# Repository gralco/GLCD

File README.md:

Reimplementation of the RepRapDiscount Full Graphic Smart Controller in KiCad

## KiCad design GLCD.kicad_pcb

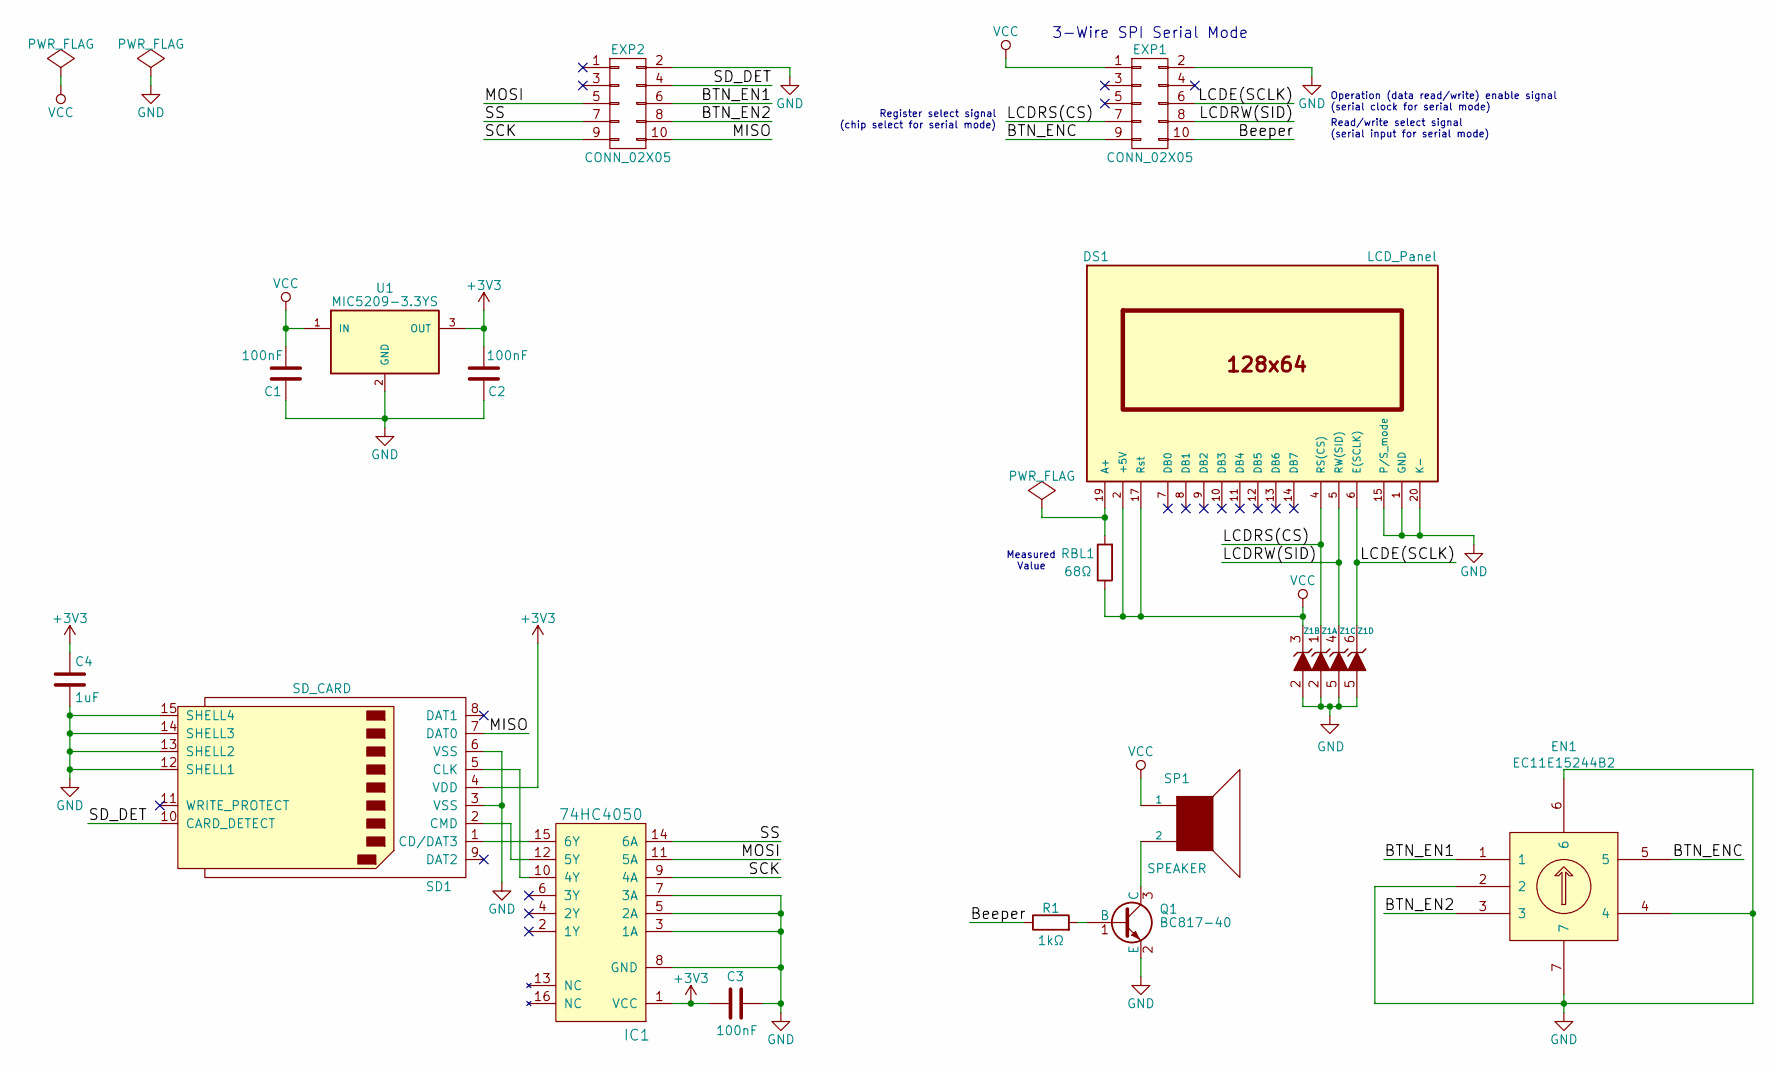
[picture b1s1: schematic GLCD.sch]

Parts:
C1, C2, C3: 100nF; C_0805_HandSoldering; Tolerance 10%; MFG Part Num 08055C104KAT2A
C4: 1uF; C_1206_HandSoldering; Tolerance 5%; MFG Part Num VJ1206Y105JXJTW1BC
DS1: LCD_Panel; Pin_Header_Straight_1x20; MFG Part Num ST7920
EN1: EC11E15244B2; Rotary_Encoder; MFG Part Num EC11E15244B2
EXP1, EXP2: CONN_02X05; IDC_Header_Straight_10pins; MFG Part Num 30310-6002HB
IC1: 74HC4050; SO-16-N; MFG Part Num CD74HC4050M96
Q1: BC817-40; SOT-23_Handsoldering; MFG Part Num BC817-40-7-F
R1: 1kΩ; R_0805_HandSoldering; Tolerance 1%; MFG Part Num CRCW08051K00FKEA
RBL1: 68Ω; R_0805_HandSoldering; Tolerance 5%; MFG Part Num ERJ-6GEYJ680V
SD1: SD_CARD; SD_Card_Receptacle; MFG Part Num 2041021-4
SP1: SPEAKER; Buzzer_12x9.5RM7.6; MFG Part Num AI-1223-TWT-5V-R
U1: MIC5209-3.3YS; SOT-223; MFG Part Num MIC5209-3.3YS-TR
Z1: ZENER_4_CHANNEL; SOT-666; MFG Part Num UCLAMP0504A.TCT

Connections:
+3V3: C2.1, C3.1, C4.1, IC1.1 (VCC), SD1.4 (VDD), U1.3 (OUT)
/BTN_EN1: EN1.1, EXP2.6
/BTN_EN2: EN1.3, EXP2.8
/BTN_ENC: EN1.5, EXP1.9
/Beeper: EXP1.10, R1.1
/LCDE(SCLK): DS1.6 (E(SCLK)), EXP1.6, Z1.6 (K)
/LCDRS(CS): DS1.4 (RS(CS)), EXP1.7, Z1.1 (K)
/LCDRW(SID): DS1.5 (RW(SID)), EXP1.8, Z1.4 (K)
/MISO: EXP2.10, SD1.7 (DAT0)
/MOSI: EXP2.5, IC1.11 (5A)
/SCK: EXP2.9, IC1.9 (4A)
/SD_DET: EXP2.4, SD1.10 (CARD_DETECT)
/SS: EXP2.7, IC1.14 (6A)
GND: C1.2, C2.2, C3.2, C4.2, DS1.1 (GND), DS1.15 (P/S_mode), DS1.20 (K-), EN1.2, EN1.4, EN1.6, EN1.7, EXP1.2, EXP2.2, IC1.3 (1A), IC1.5 (2A), IC1.7 (3A), IC1.8 (GND), Q1.2 (E), SD1.3 (VSS), SD1.6 (VSS), SD1.12 (SHELL1), SD1.13 (SHELL2), SD1.14 (SHELL3), SD1.15 (SHELL4), U1.2 (GND), U1.4, Z1.2 (A), Z1.5 (A)
unnamed: DS1.19 (A+), RBL1.2
unnamed: IC1.10 (4Y), SD1.5 (CLK)
unnamed: IC1.12 (5Y), SD1.2 (CMD)
unnamed: IC1.15 (6Y), SD1.1 (CD/DAT3)
unnamed: Q1.1 (B), R1.2
unnamed: Q1.3 (C), SP1.2
VCC: C1.1, DS1.2 (+5V), DS1.17 (Rst), EXP1.1, RBL1.1, SP1.1, U1.1 (IN), Z1.3 (K)

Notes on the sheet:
Operation (data read/write) enable signal (serial clock for serial mode)
Read/write select signal (serial input for serial mode)
Register select signal (chip select for serial mode)
3-Wire SPI Serial Mode
Measured Value

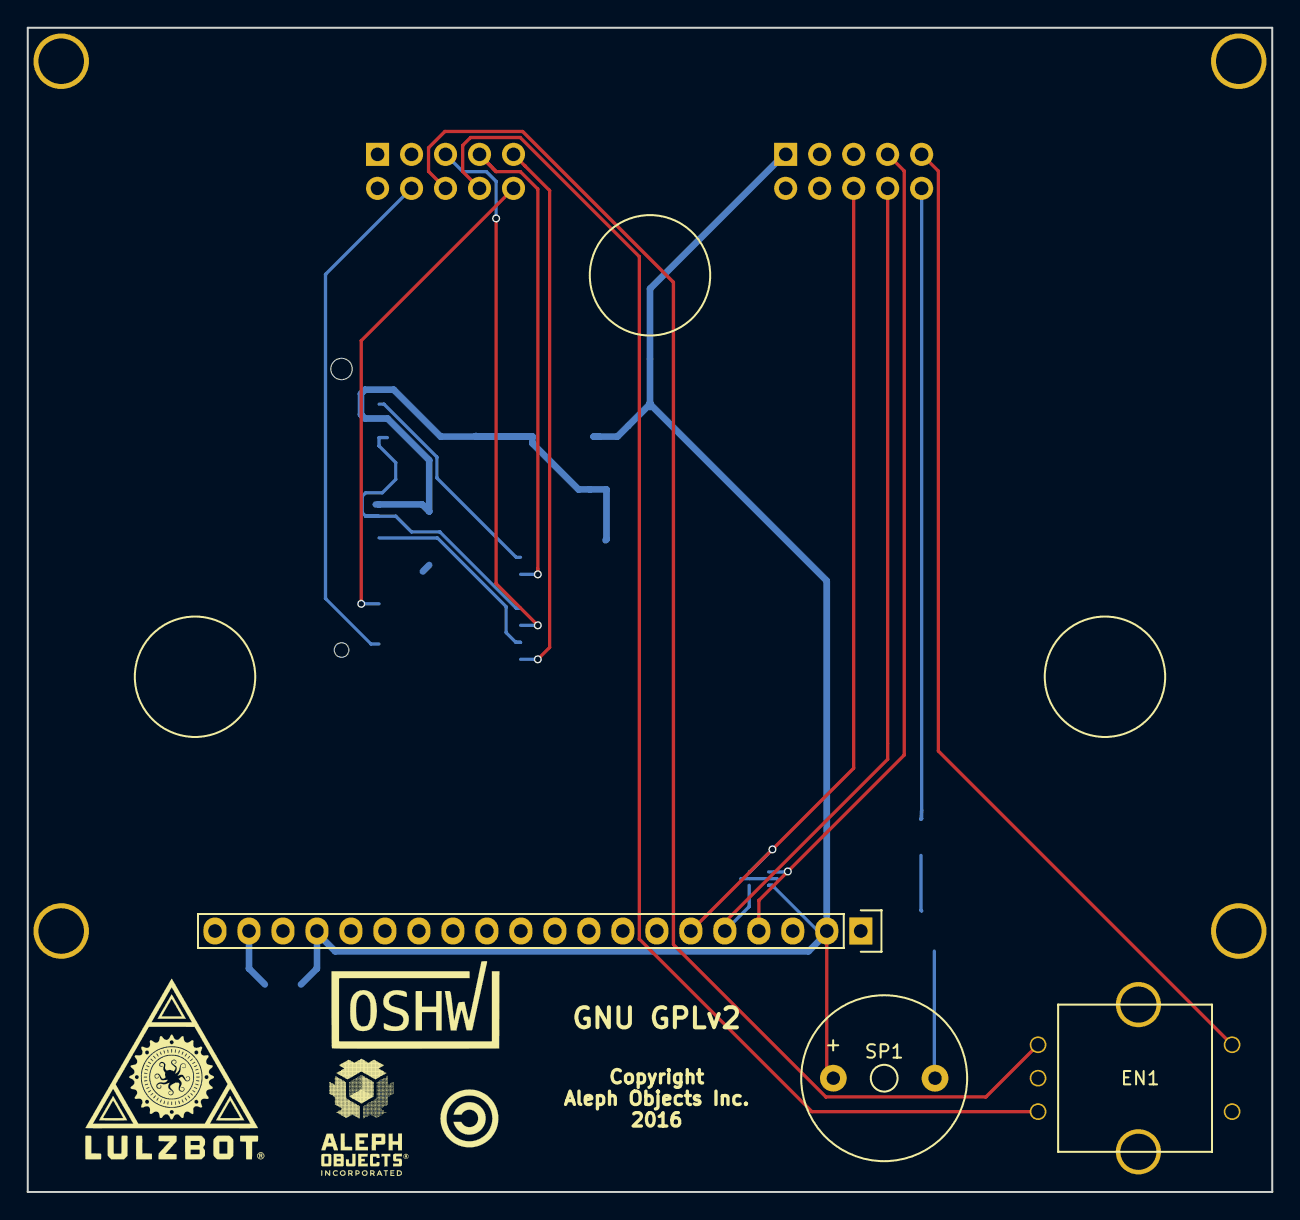
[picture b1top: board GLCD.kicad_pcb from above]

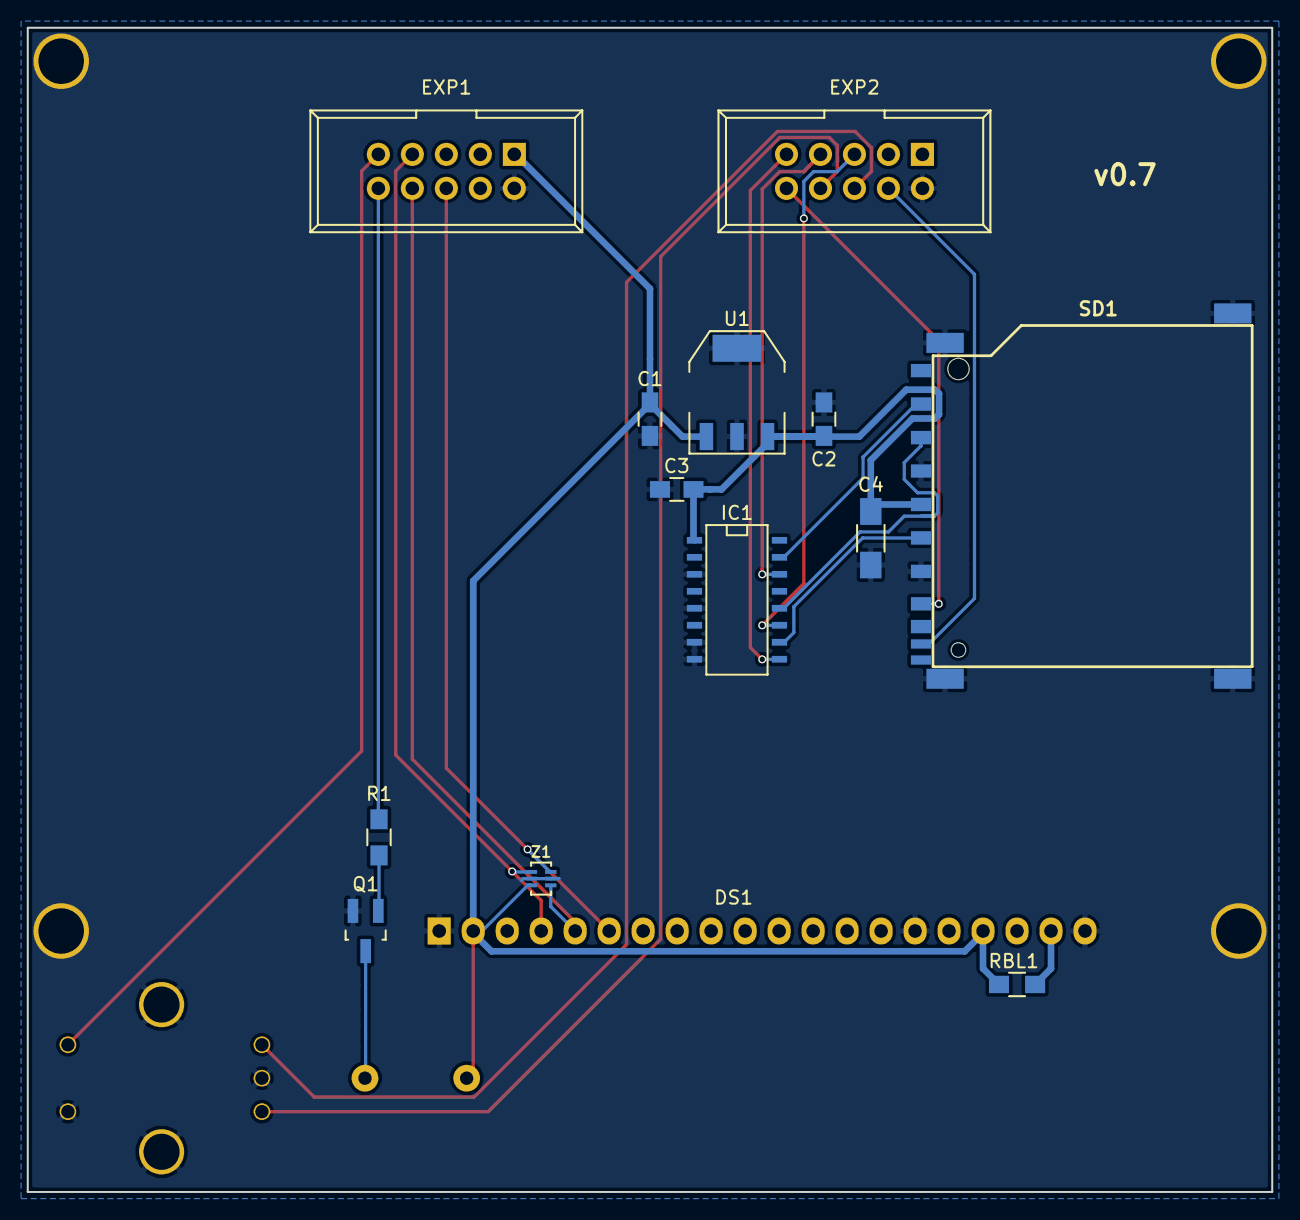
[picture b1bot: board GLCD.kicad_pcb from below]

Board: 2 copper layers, 93.0 x 87.0 mm, 16 parts (13 on the bottom side), 21 nets.

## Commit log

2017-10-08 Add all project files

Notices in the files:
GLCD.kicad_pcb:
GNU GPLv2, Copyright 2016
GNU GPLv2
